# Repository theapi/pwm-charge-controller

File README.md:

# PWM Charge Controller

PWM solar charge controller, with common ground.

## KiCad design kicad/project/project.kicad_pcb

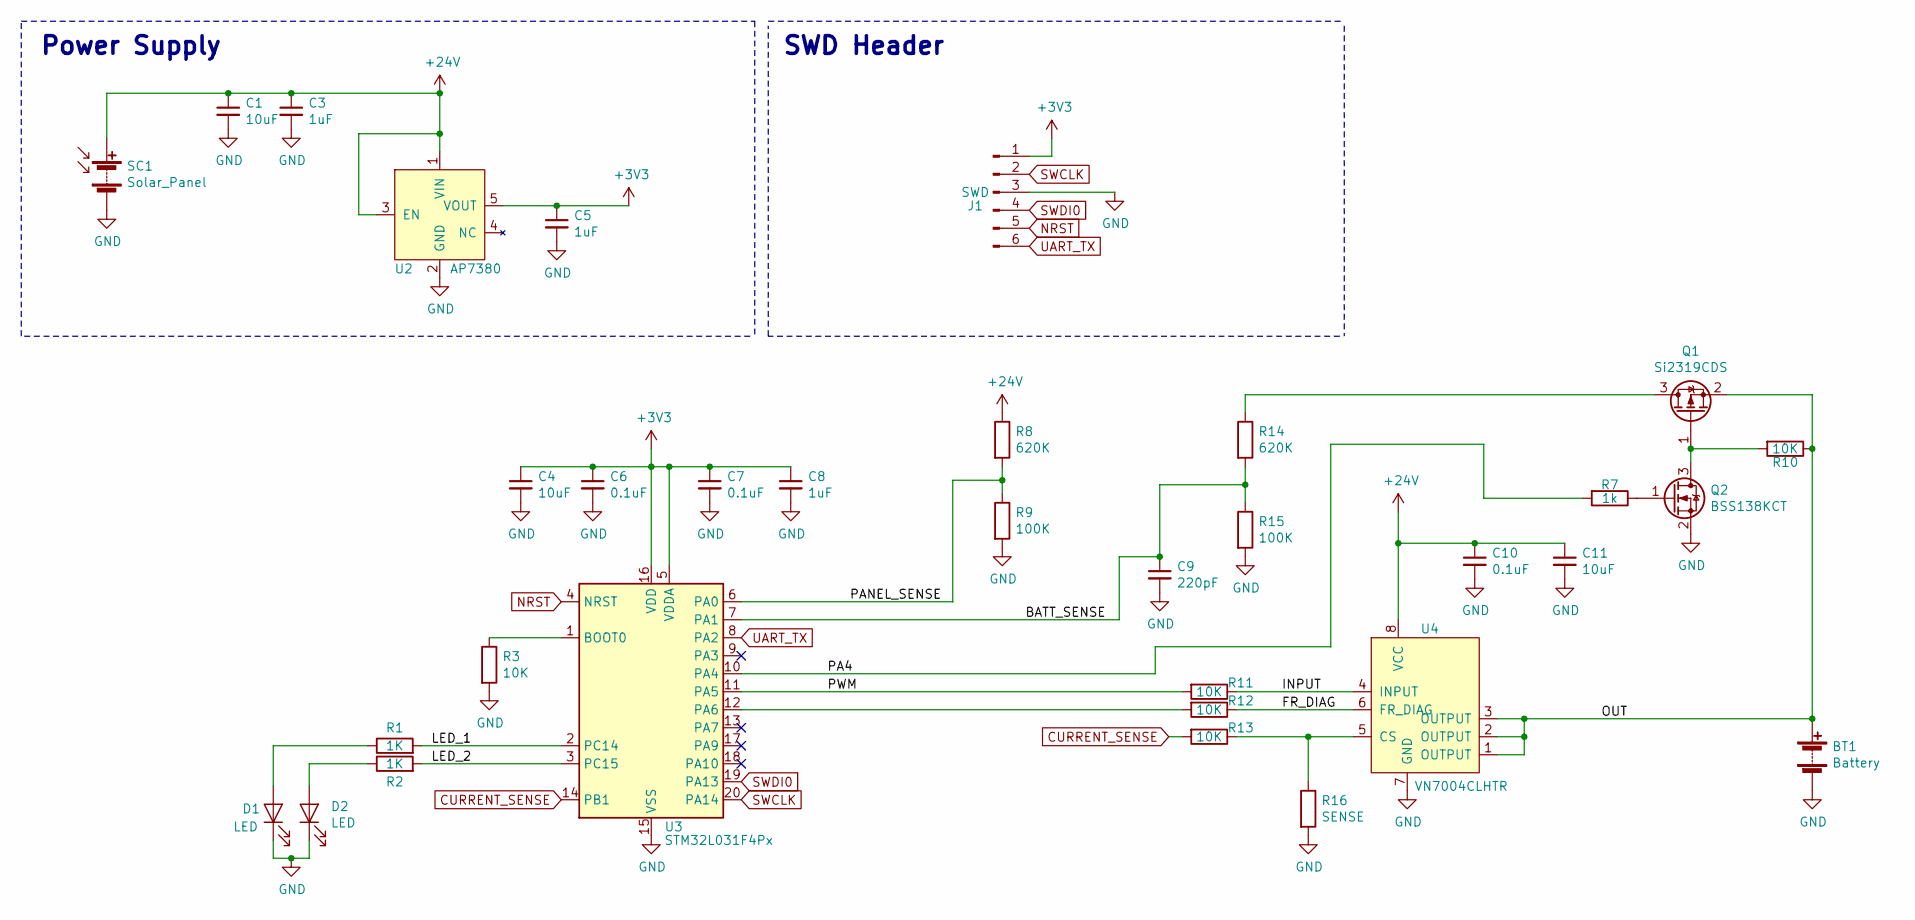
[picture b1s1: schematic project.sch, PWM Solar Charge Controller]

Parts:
BT1: Battery; TerminalBlock_bornier-2_P5.08mm
C1, C4, C11: 10uF; C_0603_1608Metric_Pad1.05x0.95mm_HandSolder
C3, C5, C8: 1uF; C_0603_1608Metric_Pad1.05x0.95mm_HandSolder
C6, C7, C10: 0.1uF; C_0603_1608Metric_Pad1.05x0.95mm_HandSolder
C9: 220pF; C_0603_1608Metric_Pad1.05x0.95mm_HandSolder
D1, D2: LED; LED_0805_2012Metric_Pad1.15x1.40mm_HandSolder
J1: SWD; PinHeader_1x06_P2.54mm_Vertical
Q1: Si2319CDS; SOT-23
Q2: BSS138KCT; SOT-23
R1, R2: 1K; R_0603_1608Metric_Pad1.05x0.95mm_HandSolder
R3, R10, R11, R12, R13: 10K; R_0603_1608Metric_Pad1.05x0.95mm_HandSolder
R7: 1k; R_0603_1608Metric_Pad1.05x0.95mm_HandSolder
R8, R14: 620K; R_0603_1608Metric_Pad1.05x0.95mm_HandSolder
R9, R15: 100K; R_0603_1608Metric_Pad1.05x0.95mm_HandSolder
R16: SENSE; R_0805_2012Metric_Pad1.15x1.40mm_HandSolder
SC1: Solar_Panel; TerminalBlock_bornier-2_P5.08mm
U2: AP7380; SOT-23-5_HandSoldering
U3: STM32L031F4Px; TSSOP-20_4.4x6.5mm_P0.65mm
U4: VN7004CLHTR; Octapak

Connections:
+3V3: C4.1, C5.1, C6.1, C7.1, C8.1, J1.1, U2.5 (VOUT), U3.5 (VDDA), U3.16 (VDD)
+24V: C1.1, C3.1, C10.1, C11.1, R8.1, SC1.1 (+), U2.1 (VIN), U2.3 (EN), U4.8 (VCC)
/BATT_SENSE: C9.1, R14.2, R15.1, U3.7 (PA1)
/FR_DIAG: R12.1, U4.6 (FR_DIAG)
/INPUT: R11.1, U4.4 (INPUT)
/LED_1: R1.2, U3.2 (PC14)
/LED_2: R2.2, U3.3 (PC15)
/OUT: BT1.1 (+), Q1.2 (S), R10.1, U4.1 (OUTPUT), U4.2 (OUTPUT), U4.3 (OUTPUT)
/PA4: R7.2, U3.10 (PA4)
/PANEL_SENSE: R8.2, R9.1, U3.6 (PA0)
/PWM: R11.2, U3.11 (PA5)
CURRENT_SENSE: R13.2, U3.14 (PB1)
GND: BT1.2 (-), C1.2, C3.2, C4.2, C5.2, C6.2, C7.2, C8.2, C9.2, C10.2, C11.2, D1.1 (K), D2.1 (K), J1.3, Q2.2 (S), R3.2, R9.2, R15.2, R16.2, SC1.2 (-), U2.2 (GND), U3.15 (VSS), U4.7 (GND)
NRST: J1.5, U3.4 (NRST)
unnamed: D1.2 (A), R1.1
unnamed: D2.2 (A), R2.1
unnamed: Q1.1 (G), Q2.3 (D), R10.2
unnamed: Q1.3 (D), R14.1
unnamed: Q2.1 (G), R7.1
unnamed: R3.1, U3.1 (BOOT0)
unnamed: R12.2, U3.12 (PA6)
unnamed: R13.1, R16.1, U4.5 (CS)
SWCLK: J1.2, U3.20 (PA14)
SWDI0: J1.4, U3.19 (PA13)
UART_TX: J1.6, U3.8 (PA2)

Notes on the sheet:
Power Supply
SWD Header

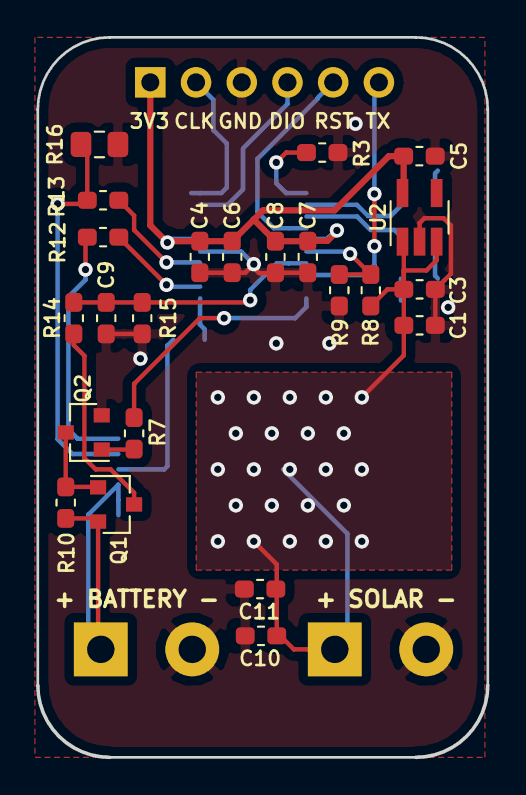
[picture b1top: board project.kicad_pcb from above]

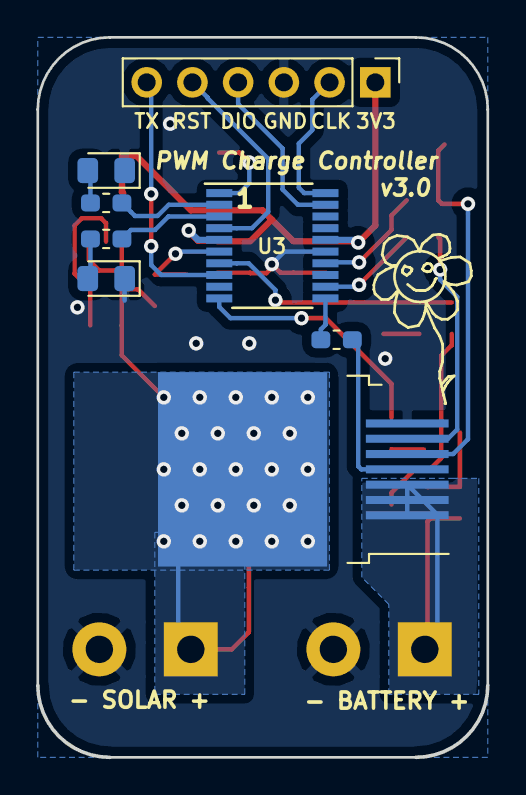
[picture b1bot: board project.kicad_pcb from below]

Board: 2 copper layers, 25.0 x 40.0 mm, 33 parts (10 on the bottom side), 25 nets.

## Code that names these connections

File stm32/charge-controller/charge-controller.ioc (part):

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Mcu.Name=STM32L031F(4-6)Px
Mcu.Package=TSSOP20
Mcu.UserName=STM32L031F4Px
PA0-CK_IN.Mode=INM
PA0-CK_IN.Signal=COMP1_INM
PA1.Signal=SharedAnalog_PA1
PA13.Mode=Serial_Wire
PA13.Signal=SYS_SWDIO
PA14.Mode=Serial_Wire
PA14.Signal=SYS_SWCLK
PA4.Signal=GPIO_Output
PA5.GPIOParameters=GPIO_Label
PA5.GPIO_Label=PWM
PA5.Signal=S_TIM2_CH1
PA6.Signal=GPIO_Output
PC14-OSC32_IN.GPIOParameters=GPIO_Label
PC14-OSC32_IN.GPIO_Label=LED_1
PC14-OSC32_IN.Signal=GPIO_Output
PC15-OSC32_OUT.GPIOParameters=GPIO_Label
PC15-OSC32_OUT.GPIO_Label=LED_2
PC15-OSC32_OUT.Signal=GPIO_Output
RCC.HSE_VALUE=8000000
RCC.SYSCLKFreq_VALUE=2097000
board=custom

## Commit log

2019-01-23 PWM at 10.4kHz
2019-01-23 Low pass filter
2019-01-23 Updated report
2019-01-24 8MHz clock
2019-01-24 UART debug
2019-02-24 About 60us rise and fall time
2019-02-24 Datasheets
2019-03-02 Start of hardware
2019-03-02 AP7380 voltage regulator
2019-03-03 Removed temperature sensor
2019-03-03 Schematic
2019-03-03 Schottky
2019-03-03 Footprints
2019-03-06 Placing parts
2019-03-07 Panel mount meter
2019-03-09 Components placed
2019-03-09 Main power traces
2019-03-09 Connections
2019-03-09 Connected
2019-03-09 Avoid power fills
2019-03-09 Zone priorities
2019-03-09 Tidying
2019-03-10 Changed diode footprint
2019-03-10 Grounds
2019-03-10 SWD header
2019-03-10 Input copper pour re-shape
2019-03-10 Sense battery before the diode
2019-03-10 Voltmeter header
2019-03-13 Solder mask
2019-03-13 Labels
2019-03-14 Mounting holes
2019-03-14 Silkscreen
2019-03-16 Bit more room for the meter
2019-03-16 Gerbers
2019-04-03 Corrected octopak footprint
2019-04-04 Testing real hardware
2019-04-07 Start of external ADC
2019-04-07 Basic output voltage control
2019-04-09 BATT_SENSE RC filter fix
2019-04-09 Measure after the diode to get the battery voltage
2019-04-11 Removed extra resistor
2019-04-14 Battery voltage switched to the ADC
2019-04-14 Pull up
2019-04-20 Tuning
2019-04-20 Use the internal ADC
2019-05-05 Average reading
2019-05-05 Faster & no UART
2019-05-05 Faster
2019-05-05 Bit slower
2019-05-11 PWM for the charge pump
2019-05-11 Mosfet PWM 499Hz
2019-05-14 Start of PWM5 schematic
2019-05-15 PWM5 Schematic
2019-05-15 Start of layout
2019-05-16 Initial board layout
2019-05-18 Clearer schematic
2019-05-18 Board outline
2019-05-18 Center layout
2019-05-18 Simulated circuit
2019-05-18 Logos
2019-05-19 Allow for solid connection to mosfet
2019-05-19 Heart to go in the potting mould
2019-05-19 Layout change
2019-05-21 Test points
2019-05-21 SOD 123F
2019-05-21 diode label
2019-06-02 LEDs on
2019-06-02 2MHz
2019-06-04 Calibrate the ADC
2019-06-04 Keep battery to set point
2019-06-05 Flashing leds
2019-06-05 Indicate the PWM duty cycle
2019-06-05 Only try to charge if there is enough voltage on the panel
2019-06-08 PWR_REGULATOR_VOLTAGE_SCALE3
2019-06-09 Set point 13500
2019-06-22 resistors
2019-06-22 VN7004CLHTR
2019-06-22 CubeMX update
2019-06-22 New layout
2019-06-23 power
2019-06-23 Power ground
2019-06-23 layout tweak
2019-06-23 mosfet change
2019-06-25 131Hz PWM 2MHz clock
2019-06-26 Flashin leds
2019-07-05 Corrected mosfet labels
2019-07-06 Swapped the leds
2019-07-22 Basic operation
2019-07-22 Status LED
2019-08-11 Migrate to STM32CubeIDE
2019-08-11 ADC via DMA & comparator
2019-08-11 Only one ADC input
2019-08-17 Large battery sense cap & larger sample buffer
